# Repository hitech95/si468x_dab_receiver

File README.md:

# SI468x DAB Receiver modules and design files
## To compile modules install kernel headers
```console
sudo apt-get install -y raspberrypi-kernel-headers
```
then run
```console
sudo install.sh
```
and reboot, that's it. Take care of the Device-Tree
### Without a PLL not all MCLK and  BCLK combinations are supported
add the alsa configuration
```console
sudo cp /home/pi/rpi-receiver-linux-rpi-*/asound.conf /etc/
```
## SI468x Firmware
unfortunately the firmware is closed source. You can buy an EVAL Board to get old ones (that is what I did).
Copy files:
```console
sudo cp -r /home/pi/rpi-receiver-linux-rpi-*/si468x /lib/firmware
```
You can copy the files to the connected EEPROM:
```console
echo fm | sudo tee /sys/devices/platform/soc/*.i2c/i2c-1/1-0064/si468x_nvram
```
copies the fm firmware referenced from the devicetree to the nvram
## Tuning
### You can use the v4l2 tools
```console
v4l2-ctl -d /dev/radio0 --set-freq=88.80
```
tunes to FM 88.8MHz.
### Search next station
```console
v4l2-ctl -d /dev/radio0 --freq-seek=dir=1,wrap=1 && v4l2-ctl -d /dev/radio0 --get-freq
```
### Adjusting volume
```console
v4l2-ctl -d /dev/radio0 --set-ctrl volume=63
```
sets the volume and activates the analog output of the SI468x
### Tuning to DAB
simply use a frequency in the DAB Band
```console
v4l2-ctl -d /dev/radio0 --freq-seek=low=187.072,high=3412,spacing=0 && cat /sys/devices/platform/soc/*.i2c/i2c-1/1-0064/si468x_service_list
```
will also print a service list

Service List:
| MHz | Service ID | SubChId | FIC | Strength | Country | Version | started | Label |
| --- | --- | --- | --- | --- | --- | --- | --- | --- |
| 187.072 | 3153 | 2 | 100 | 43 | 10 | 46 | - | ENERGY |
| 187.072 | 989 | 1 | 100 | 43 | 10 | 46 | - | R.Maria |
| 187.072 | 3416 | 10 | 100 | 43 | 10 | 46 | - | WELLE 1 |
| 187.072 | 3154 | 9 | 100 | 43 | 10 | 46 | - | Stephans Klassik |
| 187.072 | 3413 | 12 | 100 | 43 | 10 | 46 | - | Mein Kinderradio |
| 187.072 | 3364 | 8 | 100 | 43 | 10 | 46 | - | ERF Plus | 
| 187.072 | 3370 | 7 | 100 | 43 | 10 | 46 | - | Technikum ONE |
| 187.072 | 3367 | 6 | 100 | 43 | 10 | 46 | - | Rock Antenne |
| 187.072 | 3414 | 3 | 100 | 43 | 10 | 46 | - | j▒.live |
| 187.072 | 3143 | 5 | 100 | 43 | 10 | 46 | - | * 88.6 * |
| 187.072 | 3412 | 0 | 100 | 43 | 10 | 46 | * | ARABELLA RELAX |
| 187.072 | 3411 | 11 | 100 | 43 | 10 | 46 | - | KLASSIK RADIO |

use **MHz** for the **low** and **Service ID** for the **high** argument to tune with `v4l2-ctl`

### Get the dynamic label
```console
cat /sys/devices/platform/soc/*.i2c/i2c-1/1-0064/si468x_dynamic_label
```
## ToDo
  * in Austria DAB is broadcasted on a single band - never tried two bands....
  * HF receiver circuit needs to be tuned - needs time and equipment!
  * Charset is not converted (j▒.live should be jö.live), but I do not know if this makes sense in the module

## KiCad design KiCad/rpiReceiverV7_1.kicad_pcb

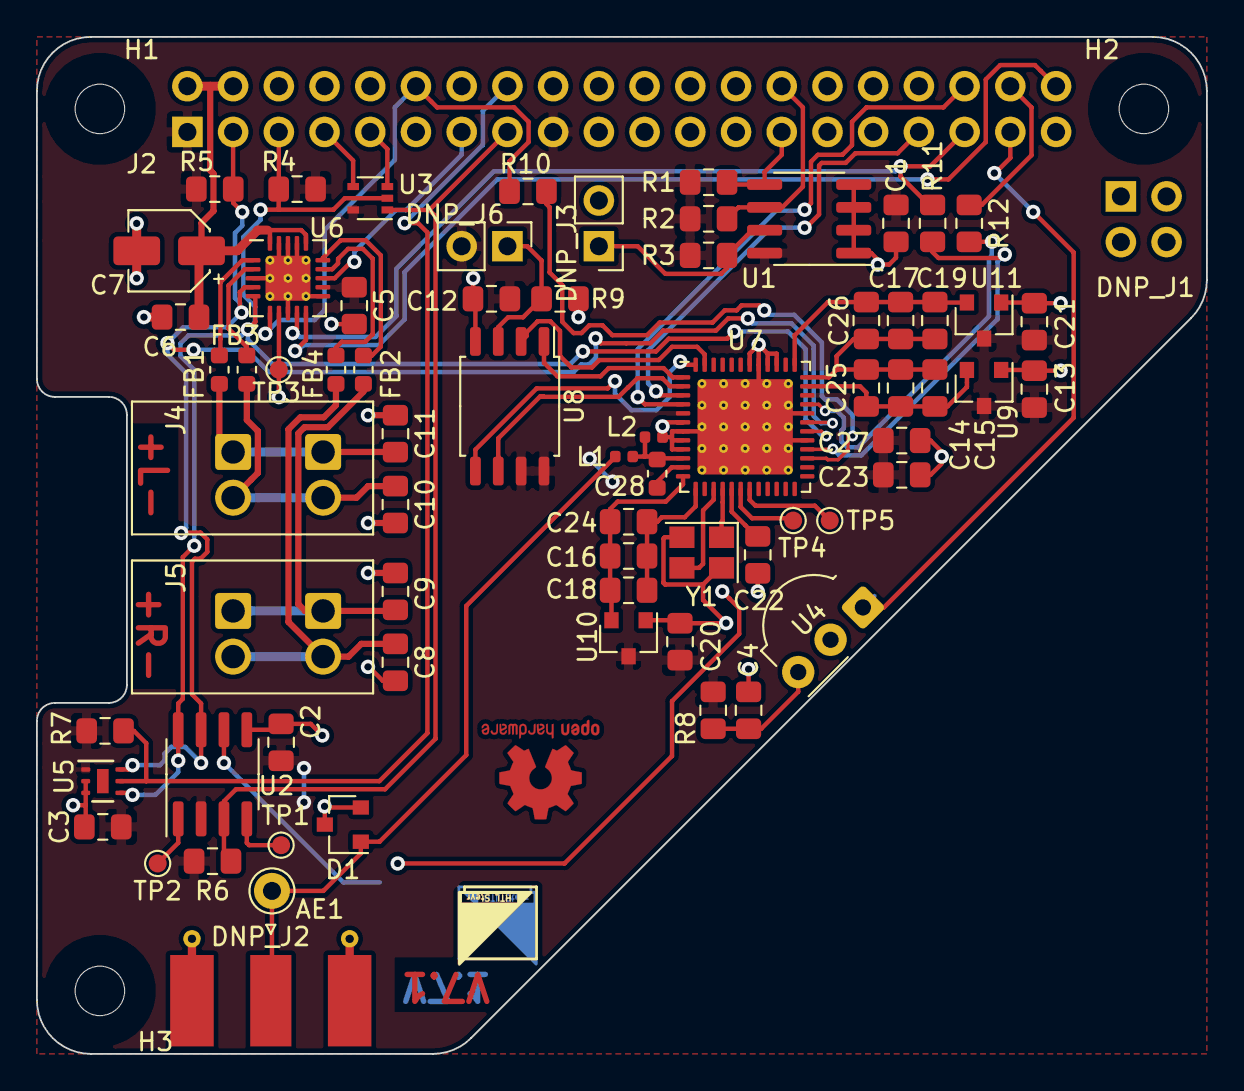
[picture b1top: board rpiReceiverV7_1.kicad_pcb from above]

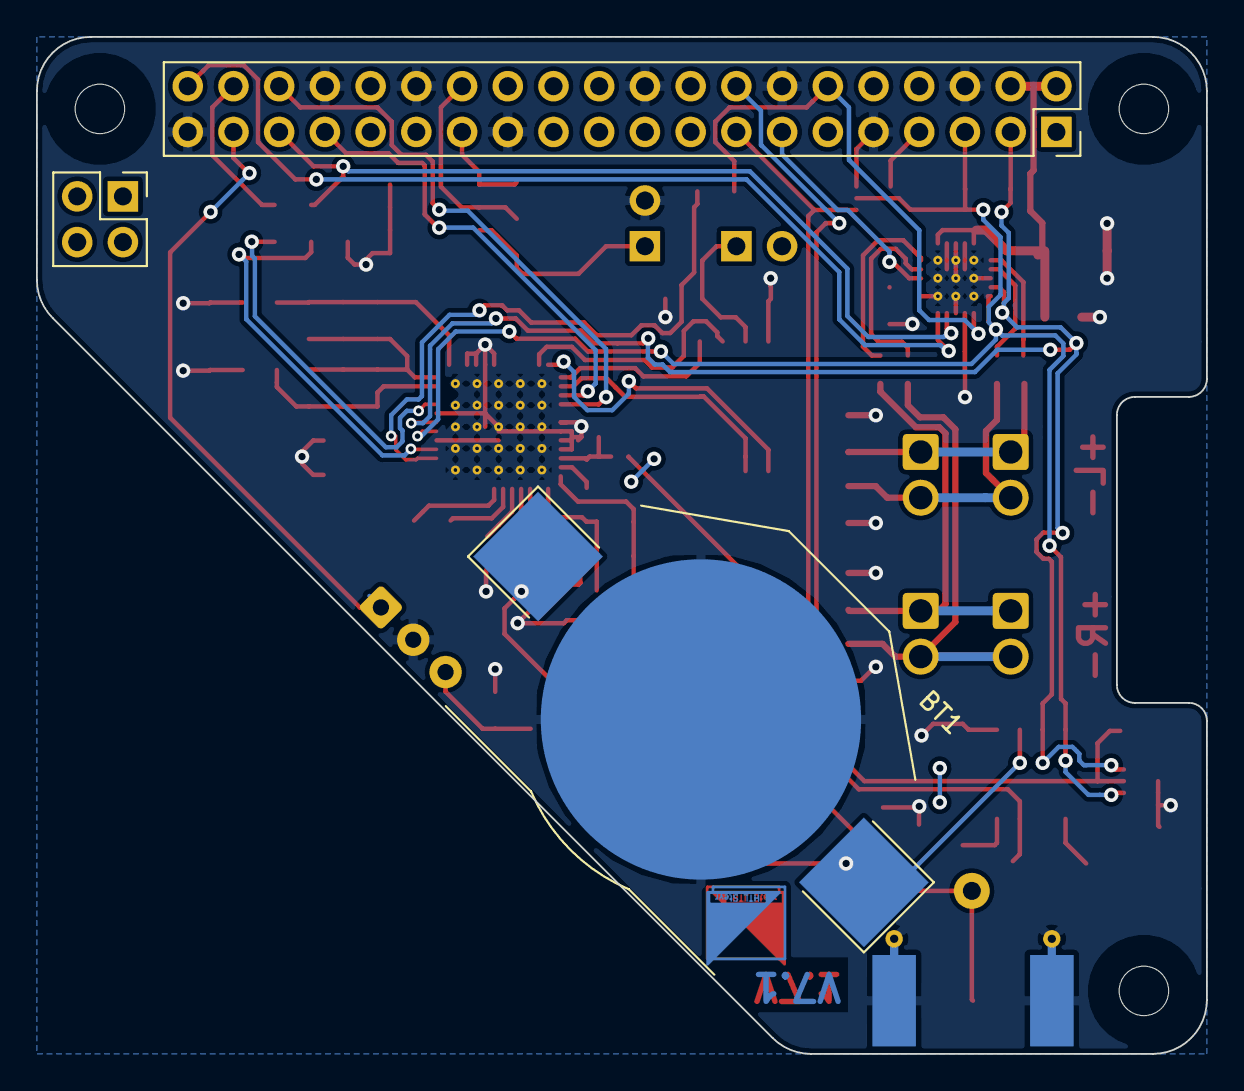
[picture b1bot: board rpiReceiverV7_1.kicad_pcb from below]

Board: 2 copper layers, 65.0 x 56.5 mm, 80 parts (4 on the bottom side), 52 nets.

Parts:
AE1: Antenna; Pin_D1.0mm_L10.0mm
BT1: Battery_Cell; BatteryHolder_Keystone_3002_1x2032
C1, C2, C3, C4, C5, C6, C12, C13, C20, C21: 100nF; C_0805_2012Metric_Pad1.15x1.40mm_HandSolder
C7: 4u7/25V; CP_Elec_4x5.4
C8, C9, C10, C11: 470p; C_0805_2012Metric_Pad1.15x1.40mm_HandSolder
C14, C16, C17, C23: 2n2; C_0805_2012Metric_Pad1.15x1.40mm_HandSolder
C15, C18, C19, C22, C27: 1uF; C_0805_2012Metric_Pad1.15x1.40mm_HandSolder
C24, C25, C26: 8p2; C_0805_2012Metric_Pad1.15x1.40mm_HandSolder
C28: 10pF; C_0603_1608Metric
D1: CM1213A-01SO; SOT-23
DNP_J1: PI4HAT; PinSocket_2x02_P2.54mm_Vertical
DNP_J2: Conn_Coaxial; SMA_Molex_73251-1153_EdgeMount_Horizontal
DNP_J3, DNP_J6: Conn_01x02; PinHeader_1x02_P2.54mm_Vertical
FB1, FB2, FB3, FB4: Ferrite_Bead_Small; L_0603_1608Metric
H1, H2, H3: MountingHole; MountingHole_2.7mm_M2.5
J2: PI40HAT; PinSocket_2x20_P2.54mm_Vertical
J4, J5: Conn_01x02; TE_2834085-1_1x02_P2.54mm_45deg
L1: 62nH; L_0402_1005Metric
L2: 120nH; L_0402_1005Metric
Logo1: OSHW-Logo2_7.3x6mm_Copper
Logo2, Logo3: HTL-Steyr-Logo_4x4mm_Copper
Logo4: HTL-Steyr-Logo_4x4mm_SilkScreen
R1, R2, R3, R4, R5, R6, R7, R9, R10, R11: 3k9; R_0805_2012Metric_Pad1.15x1.40mm_HandSolder
R8, R12: 100; R_0805_2012Metric_Pad1.15x1.40mm_HandSolder
TP1, TP2, TP3: TestPoint; TestPoint_Pad_D1.0mm
TP4, TP5: TestPoint_Flag; TestPoint_Pad_D1.0mm
U1: CAT24C512; SOIC-8_3.9x4.9mm_P1.27mm
U2: DS3231MZ; SOIC-8_3.9x4.9mm_P1.27mm
U3: 74AHC1G66; SOT-353_SC-70-5
U4: TSOP43xx; Vishay_MOLD-3Pin
U5: OPT3001; DNP-6-1EP_2.1x2.1mm_P0.65mm_EP0.65x1.35mm
U6: SSM2518; LFCSP-20-1EP_4x4mm_P0.5mm_EP2.5x2.5mm_ThermalVias
U7: Si4688-A10-GM; QFN-48-1EP_7x7mm_P0.5mm_EP5.3x5.3mm_ThermalVias
U8: SST25VF016B-50-4x-S2Ax; SOIC-8_5.275x5.275mm_P1.27mm
U9, U10, U11: AP2127N-1.8; SOT-23
Y1: Crystal_GND24_Small; Crystal_SMD_Abracon_ABM8G-4Pin_3.2x2.5mm

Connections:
+3V3: C1.1, C2.1, C3.1, C5.1, C12.2, C13.1, C20.1, C21.1, C23.1, C27.1, DNP_J6.2, J2.1, J2.17, R1.2, R2.2, R3.2, R4.2, R5.2, R6.2, R7.2, R8.2, U1.8, U2.2, U3.5, U5.1, U6.12, U7.5, U7.34, U8.7, U8.8, U9.3, U10.3, U11.3
+5V: C6.1, C7.1, J2.2, J2.4, U6.16, U6.20
/GPIO04: J2.7, U3.4
/GPIO13: J2.33, U7.3
/GPIO16: J2.36, U7.4
/GPIO18: J2.12, R10.2, U6.6
/GPIO19: J2.35, R11.2, U6.9
/GPIO20: J2.38, R12.1
/GPIO21: J2.40, U6.10
/GPIO22: J2.15, R6.1, U2.3, U3.1
/GPIO23: J2.16, R7.1, U5.5
/GPIO26: J2.37, U4.1
/GPIO27: J2.13, U6.13
/ID_SC_EEPROM: J2.28, R2.1, U1.6
/ID_SD_EEPROM: J2.27, R1.1, U1.5
/SCL1: J2.5, R4.1, U2.8, U3.2, U5.4, U6.5, U7.30
/SDA1: J2.3, R5.1, U2.7, U5.6, U6.4, U7.31
GND: BT1.2, C1.2, C2.2, C3.2, C4.1, C5.2, C6.2, C7.2, C8.2, C9.2, C10.2, C11.2, C12.1, C13.2, C20.2, C21.2, C22.1, C23.2, C27.2, D1.2, D1.3, DNP_J2.2, DNP_J3.2, J2.6, J2.9, J2.14, J2.20, J2.25, J2.30, J2.34, J2.39, L2.2, R9.1, TP3.1, U1.1, U1.2, U1.3, U1.4, U2.5, U3.3, U4.2, U5.2, U5.3, U6.3, U6.7, U6.8, U6.11, U6.17, U6.18, U6.19, U6.21, U7.6, U7.7, U7.8, U7.9, U7.29, U7.32, U7.39, U7.40, U7.41, U7.42, U7.49, U8.4, U9.1, U10.1, U11.1, Y1.2, Y1.4
unnamed: AE1.1, D1.1, DNP_J2.1, L1.2
unnamed: BT1.1, U2.6
unnamed: C4.2, R8.1, U4.3
unnamed: C8.1, FB4.1, J5.2
unnamed: C9.1, FB2.1, J5.1
unnamed: C10.1, FB3.1, J4.2
unnamed: C11.1, FB1.1, J4.1
unnamed: C14.1, C15.1, C25.1, U7.35, U9.2
unnamed: C14.2, C15.2, C17.2, C19.2, C25.2, C26.2, U7.36
unnamed: C16.1, C18.1, C24.1, U7.12, U10.2
unnamed: C16.2, C18.2, C24.2, U7.13
unnamed: C17.1, C19.1, C26.1, U7.37, U11.2
unnamed: C22.2, U7.17
unnamed: C28.1, L1.1, L2.1, U7.10
unnamed: C28.2, U7.11
unnamed: DNP_J3.1, R3.1, U1.7
unnamed: DNP_J6.1, R9.2, U8.3
unnamed: FB1.2, U6.1
unnamed: FB2.2, U6.15
unnamed: FB3.2, U6.2
unnamed: FB4.2, U6.14
unnamed: R10.1, U7.27
unnamed: R11.1, U7.28
unnamed: R12.2, U7.33
unnamed: TP1.1, U2.4
unnamed: TP2.1, U2.1
unnamed: TP4.1, U7.18
unnamed: TP5.1, U7.19
unnamed: U7.1, U8.1
unnamed: U7.2, U8.6
unnamed: U7.15, Y1.3
unnamed: U7.16, Y1.1
unnamed: U7.47, U8.2
unnamed: U7.48, U8.5

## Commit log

2021-02-21 initial release
